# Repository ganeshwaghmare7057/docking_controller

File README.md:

# Dose droid medicine packing machine (Docking controller)
  Description: Dose droid is medicine packing machine, docking controller is one part of machine. I designed PCB and I use ATmega328 controller chip. Collecting two module QRT13GR sensor and encoder. I used UART and SPI communication protocol.

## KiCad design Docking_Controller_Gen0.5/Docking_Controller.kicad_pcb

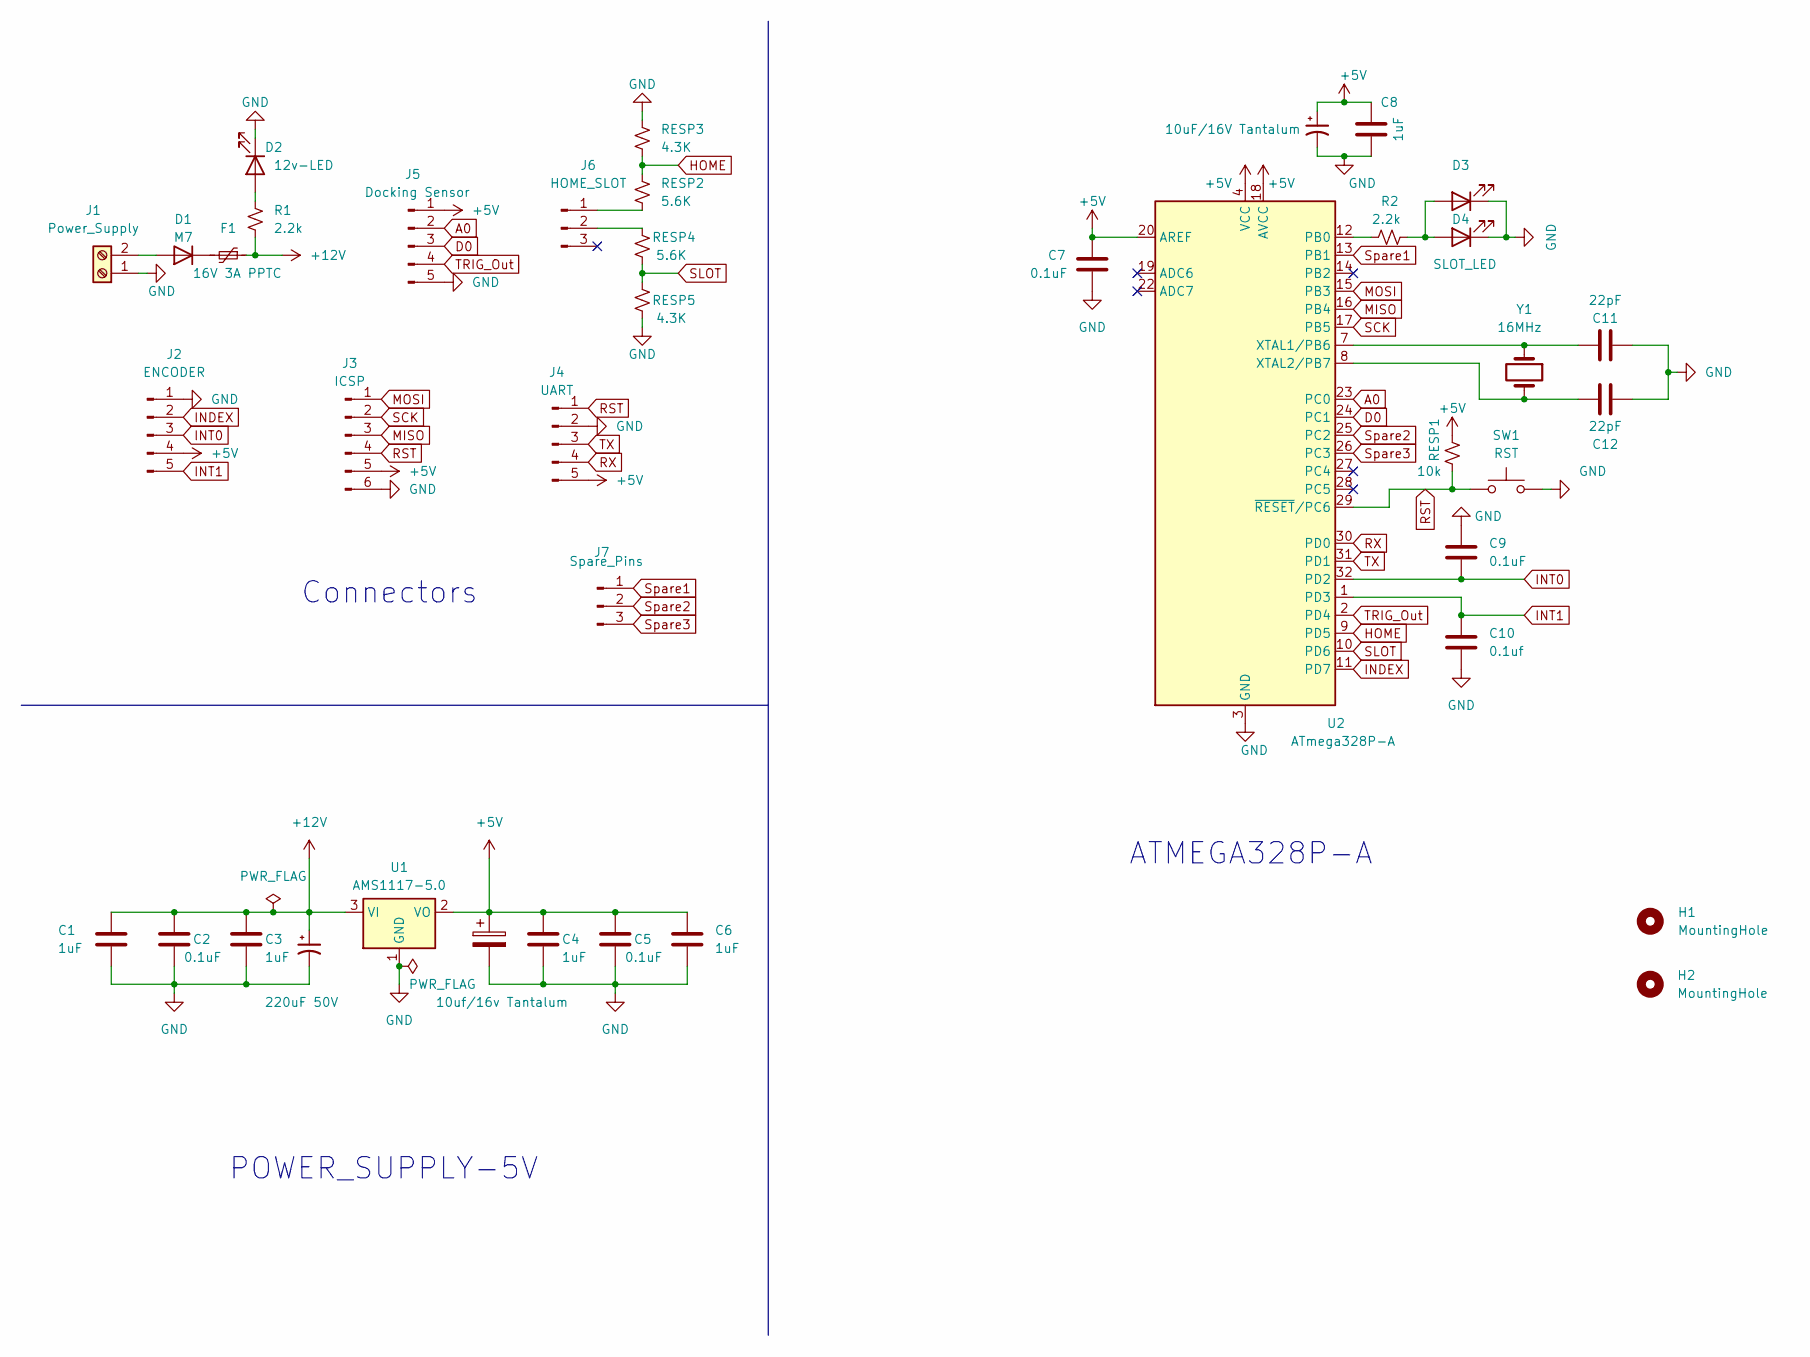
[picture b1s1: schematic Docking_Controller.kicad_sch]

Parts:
C1, C3, C4, C6, C8: 1uF; C_1206_3216Metric_Pad1.33x1.80mm_HandSolder
C2, C5, C7, C9: 0.1uF; C_0805_2012Metric_Pad1.18x1.45mm_HandSolder
C10: 0.1uf; C_0805_2012Metric_Pad1.18x1.45mm_HandSolder
C11, C12: 22pF; C_0805_2012Metric_Pad1.18x1.45mm_HandSolder
CESP1: 10uf/16v Tantalum; CP_EIA-3216-18_Kemet-A_Pad1.58x1.35mm_HandSolder
D1: M7; D_SMA_Handsoldering
D2: 12v-LED; LED_1206_3216Metric_Pad1.42x1.75mm_HandSolder
D3: SLOT_LED; LED_D3.0mm_Horizontal_O1.27mm_Z2.0mm
D4: SLOT_LED; LED_0805_2012Metric_Pad1.15x1.40mm_HandSolder
F1: 16V 3A PPTC; Fuse_1812_4532Metric_Pad1.30x3.40mm_HandSolder
H1, H2: MountingHole; MountingHole_3.2mm_M3
J1: Power_Supply; TerminalBlock_Altech_AK300-2_P5.00mm
J2: ENCODER; B5BPHSM4TBTLFSN
J3: ICSP; PinHeader_1x06_P2.54mm_Vertical
J4: UART; B5BPHSM4TBTLFSN
J5: Docking Sensor; B5BPHSM4TBTLFSN
J6: HOME_SLOT; B3BPHSM4TBTLFSN
J7: Spare_Pins; B3BPHSM4TBTLFSN
R1, R2: 2.2k; R_0805_2012Metric_Pad1.20x1.40mm_HandSolder
RESP1: 10k; R_0805_2012Metric_Pad1.20x1.40mm_HandSolder
RESP2, RESP4: 5.6K; R_0805_2012Metric_Pad1.20x1.40mm_HandSolder
RESP3, RESP5: 4.3K; R_0805_2012Metric_Pad1.20x1.40mm_HandSolder
SW1: RST; SW_Tactile_Straight_KSA0Axx1LFTR
U1: AMS1117-5.0; SOT-223-3_TabPin2
U2: ATmega328P-A; TQFP-32_7x7mm_P0.8mm
Y1: 16MHz; Crystal_HC49-U_Vertical
|1: 220uF 50V; CP_Elec_8x10.5
|2: 10uF/16V Tantalum; CP_EIA-3216-18_Kemet-A_Pad1.58x1.35mm_HandSolder

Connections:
+5V: C4.1, C5.1, C6.1, C7.1, C8.1, CESP1.1, J2.4, J3.5, J4.5, J5.1, RESP1.1, U1.2 (VO), U2.4 (VCC), U2.6 (VCC), U2.18 (AVCC), U2.20 (AREF), |2.1
+12V: C1.1, C2.1, C3.1, F1.1, R1.2, U1.3 (VI), |1.1
A0: J5.2, U2.23 (PC0)
D0: J5.3, U2.24 (PC1)
GND: C1.2, C2.2, C3.2, C4.2, C5.2, C6.2, C7.2, C8.2, C9.1, C10.2, C11.1, C12.1, CESP1.2, D2.1 (K), D3.1 (K), D4.1 (K), J1.1, J2.1, J3.6, J4.2, J5.5, RESP3.1, RESP5.1, SW1.2, U1.1 (GND), U2.3 (GND), U2.5 (GND), U2.21 (GND), |1.2, |2.2
HOME: RESP2.1, RESP3.2, U2.9 (PD5)
INDEX: J2.2, U2.11 (PD7)
INT0: C9.2, J2.3, U2.32 (PD2)
INT1: C10.1, J2.5, U2.1 (PD3)
MISO: J3.3, U2.16 (PB4)
MOSI: J3.1, U2.15 (PB3)
unnamed: D1.2 (A), J1.2
unnamed: D1.1 (K), F1.2
unnamed: D2.2 (A), R1.1
unnamed: D3.2 (A), D4.2 (A), R2.1
unnamed: J6.1, RESP2.2
unnamed: J6.2, RESP4.2
unnamed: R2.2, U2.12 (PB0)
unnamed: C11.2, U2.7 (XTAL1/PB6), Y1.1
unnamed: C12.2, U2.8 (XTAL2/PB7), Y1.2
RST: J3.4, J4.1, RESP1.2, SW1.1, U2.29 (~RESET/PC6)
RX: J4.4, U2.30 (PD0)
SCK: J3.2, U2.17 (PB5)
SLOT: RESP4.1, RESP5.2, U2.10 (PD6)
Spare1: J7.1, U2.13 (PB1); also elsewhere on the board
Spare2: J7.2, U2.25 (PC2); also elsewhere on the board
Spare3: J7.3, U2.26 (PC3); also elsewhere on the board
TRIG_Out: J5.4, U2.2 (PD4)
TX: J4.3, U2.31 (PD1)

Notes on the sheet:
Connectors
ATMEGA328P-A
POWER_SUPPLY-5V

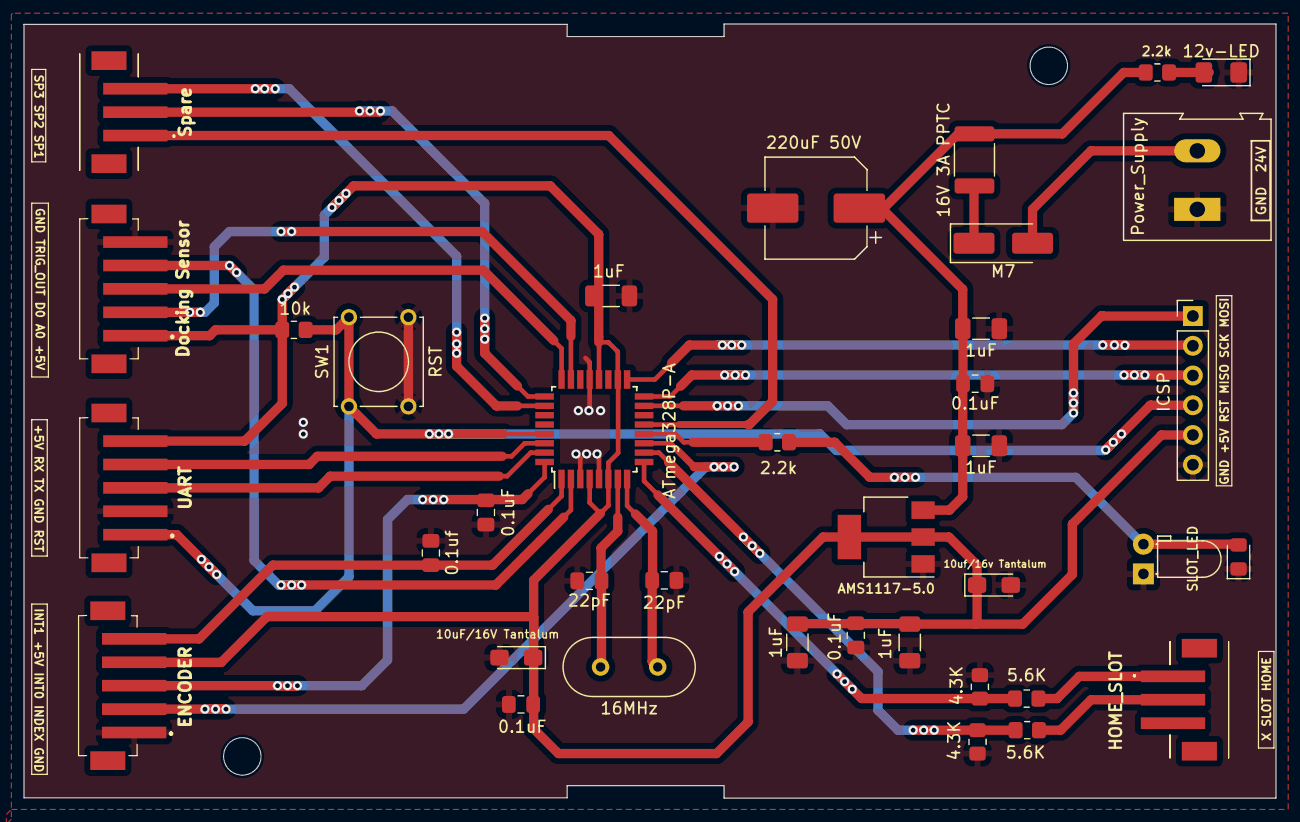
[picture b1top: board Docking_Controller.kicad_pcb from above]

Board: 2 copper layers, 107.0 x 66.1 mm, 40 parts (0 on the bottom side), 29 nets.

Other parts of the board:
Spare: Spare_Pins; B3BPHSM4TBTLFSN

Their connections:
Spare1: Spare.1; also elsewhere on the board
Spare2: Spare.2; also elsewhere on the board
Spare3: Spare.3; also elsewhere on the board

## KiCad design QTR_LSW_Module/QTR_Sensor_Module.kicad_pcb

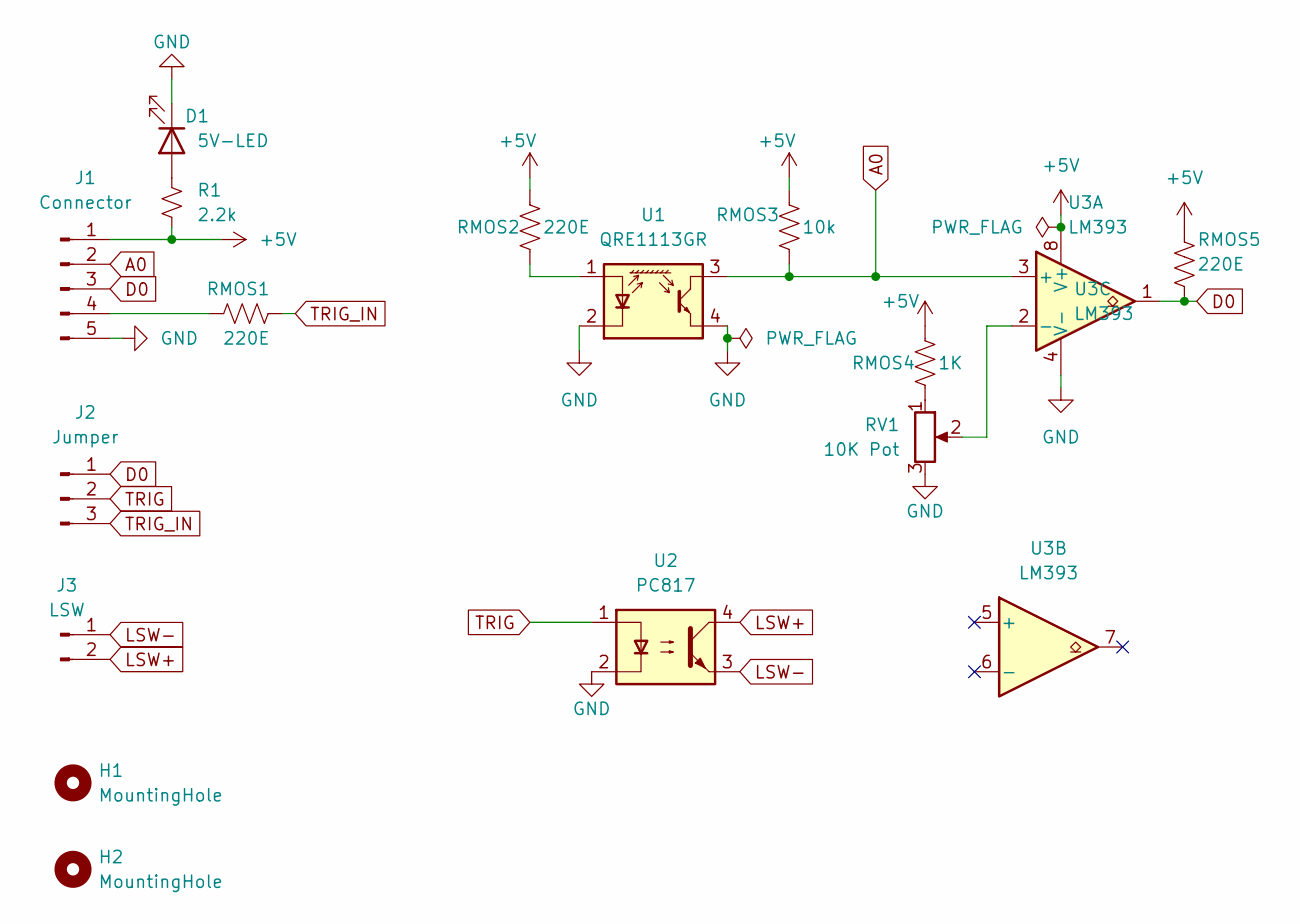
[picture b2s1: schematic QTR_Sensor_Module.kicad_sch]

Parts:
D1: 5V-LED; LED_1206_3216Metric_Pad1.42x1.75mm_HandSolder
H1, H2: MountingHole; MountingHole_2.2mm_M2
J1: Connector; B5BPHSM4TBTLFSN
J2: Jumper; PinHeader_1x03_P2.54mm_Vertical
J3: LSW; JST_PH_S2B-PH-SM4-TB_1x02-1MP_P2.00mm_Horizontal
R1: 2.2k; R_0805_2012Metric_Pad1.20x1.40mm_HandSolder
RMOS1, RMOS2, RMOS5: 220E; R_0805_2012Metric_Pad1.20x1.40mm_HandSolder
RMOS3: 10k; R_0805_2012Metric_Pad1.20x1.40mm_HandSolder
RMOS4: 1K; R_0805_2012Metric_Pad1.20x1.40mm_HandSolder
RV1: 10K Pot; TRIM_3362P-1-151
U1: QRE1113GR; OnSemi_CASE100CY
U2: PC817; DIP-4_W7.62mm
U3: LM393; SO08

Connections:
+5V: J1.1, R1.2, RMOS2.2, RMOS3.2, RMOS4.2, RMOS5.2, U3.8 (V+)
A0: J1.2, RMOS3.1, U1.3, U3.3 (+)
D0: J1.3, J2.1, RMOS5.1, U3.1
GND: D1.1 (K), J1.5, RV1.3, U1.2 (K), U1.4, U2.2, U3.4 (V-)
LSW+: J3.2, U2.4
LSW-: J3.1, U2.3
unnamed: D1.2 (A), R1.1
unnamed: J1.4, RMOS1.2
unnamed: RMOS4.1, RV1.1
unnamed: RMOS2.1, U1.1 (A)
unnamed: RV1.2, U3.2 (-)
TRIG: J2.2, U2.1
TRIG_IN: J2.3, RMOS1.1

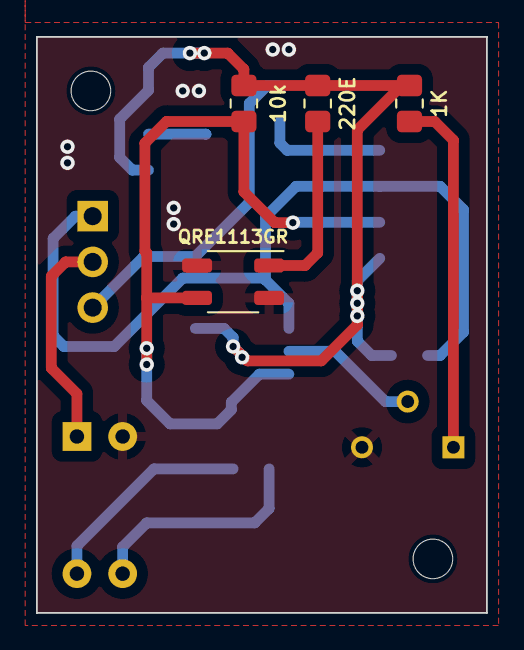
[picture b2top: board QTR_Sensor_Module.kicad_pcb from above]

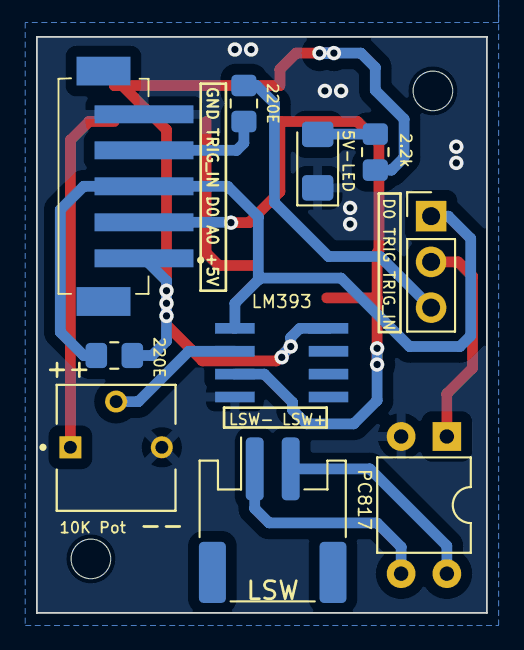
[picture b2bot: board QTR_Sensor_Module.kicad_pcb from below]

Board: 2 copper layers, 25.0 x 32.0 mm, 16 parts (10 on the bottom side), 13 nets.
